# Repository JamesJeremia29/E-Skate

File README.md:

# E-Skate
Electric powered Skate used with controller, designed with analog circuits (no microcontroller)

for Documentation, please visit link https://drive.google.com/drive/folders/10ZDVoWL7lhlL0DR7AIUaZxOVsLEZHtPU?usp=sharing

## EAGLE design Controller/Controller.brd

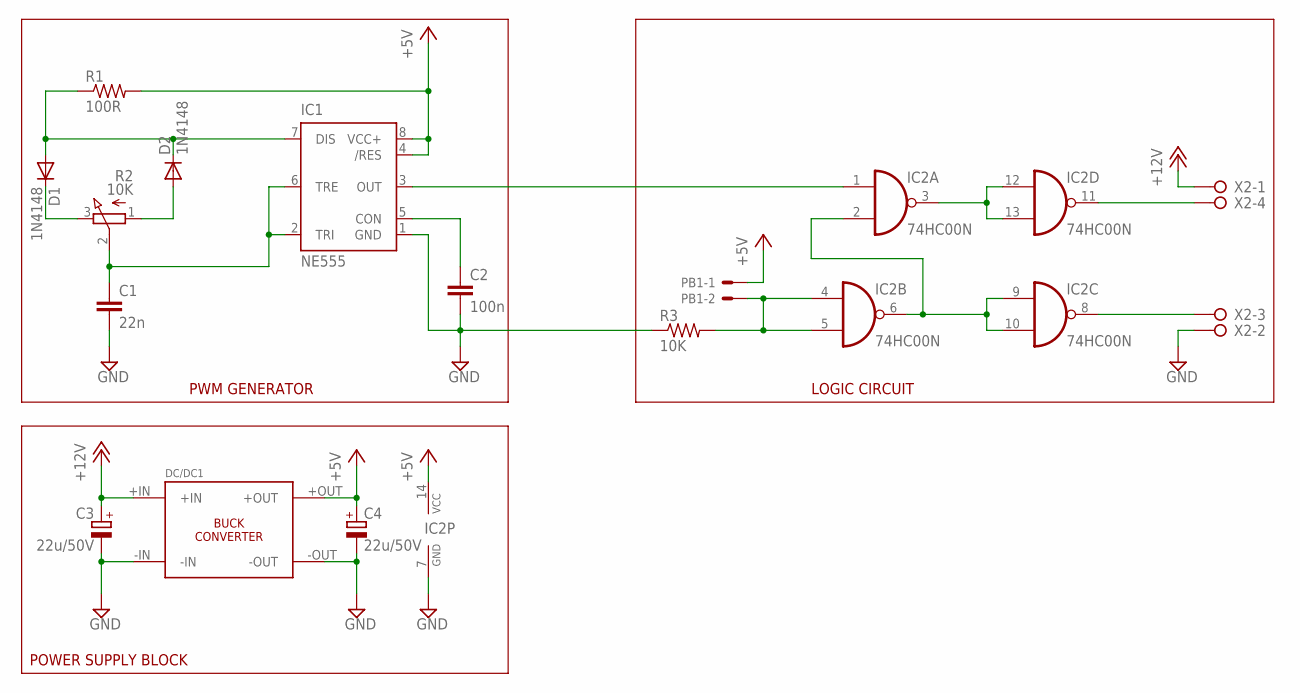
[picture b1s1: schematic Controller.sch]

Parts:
C1: 22n; C050-035X075
C2: 100n; C075-032X103
C3, C4: 22u/50V; E2,5-6
D1, D2: 1N4148; DO35-10
DC/DC1: MP1548EN
IC1: NE555; DIL-08
IC2: 74HC00N; DIL14
PB1: 22-23-2021
R1: 100R; 0207/12
R2: 10K; 3RP/1610N
R3: 10K; 0207/12
X2: W237-04P; W237-4P

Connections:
+5V: C4.+, DC/DC1.+OUT, IC1.4 (/RES), IC1.8 (VCC+), IC2.14 (VCC), PB1.1, R1.2
+12V: C3.+, DC/DC1.+IN, X2.1
GND: C1.2, C2.2, C3.-, C4.-, DC/DC1.-IN, DC/DC1.-OUT, IC1.1 (GND), IC2.7 (GND), R3.1, X2.2
unnamed: C1.1, IC1.2 (TRI), IC1.6 (TRE), R2.2 (S)
unnamed: IC1.3 (OUT), IC2.1 (I0)
unnamed: D1.C, R2.3 (E)
unnamed: D2.A, R2.1 (A)
unnamed: D1.A, D2.C, IC1.7 (DIS), R1.1
unnamed: IC2.8 (O), X2.3
unnamed: IC2.3 (O), IC2.12 (I0), IC2.13 (I1)
unnamed: C2.1, IC1.5 (CON)
unnamed: IC2.2 (I1), IC2.6 (O), IC2.9 (I0), IC2.10 (I1)
unnamed: IC2.11 (O), X2.4
unnamed: IC2.4 (I0), IC2.5 (I1), PB1.2, R3.2

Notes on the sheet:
POWER SUPPLY BLOCK
PWM GENERATOR
LOGIC CIRCUIT

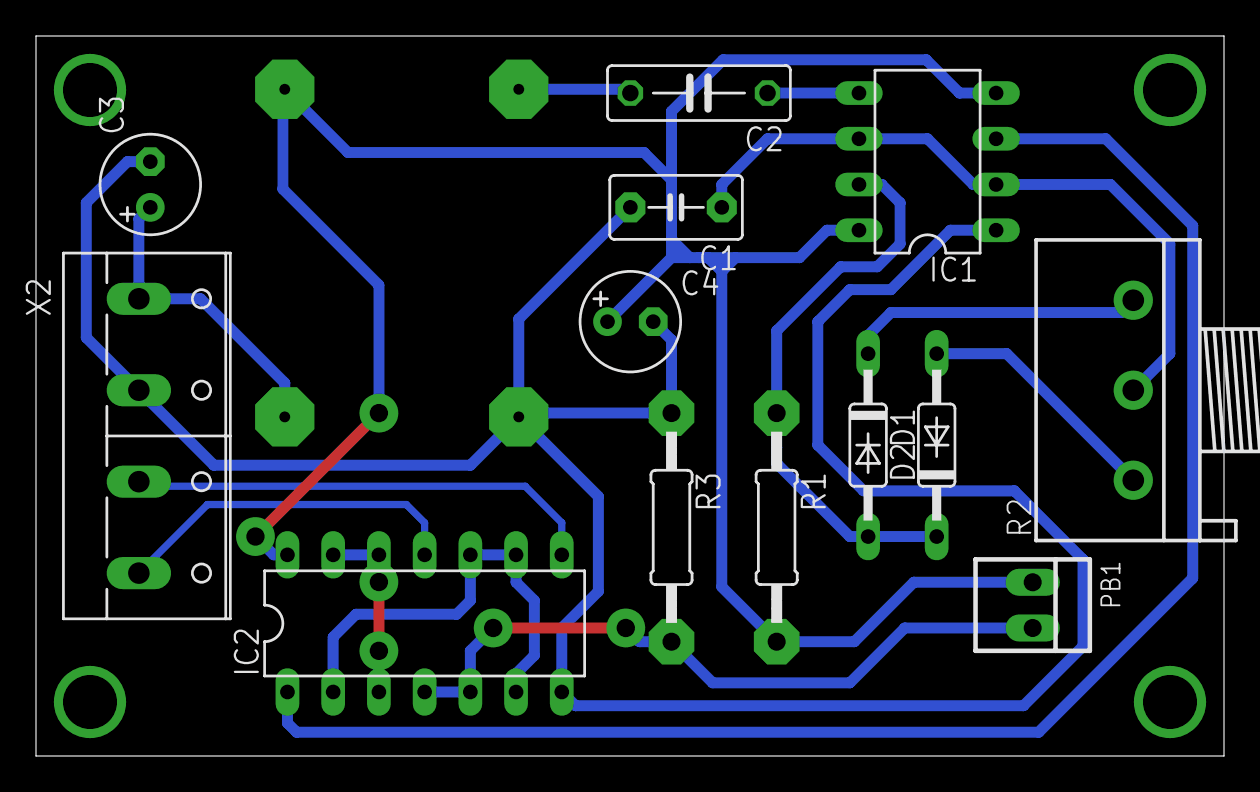
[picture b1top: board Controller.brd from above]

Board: 2 copper layers, 66.0 x 40.0 mm, 14 parts (1 on the bottom side), 14 nets.
